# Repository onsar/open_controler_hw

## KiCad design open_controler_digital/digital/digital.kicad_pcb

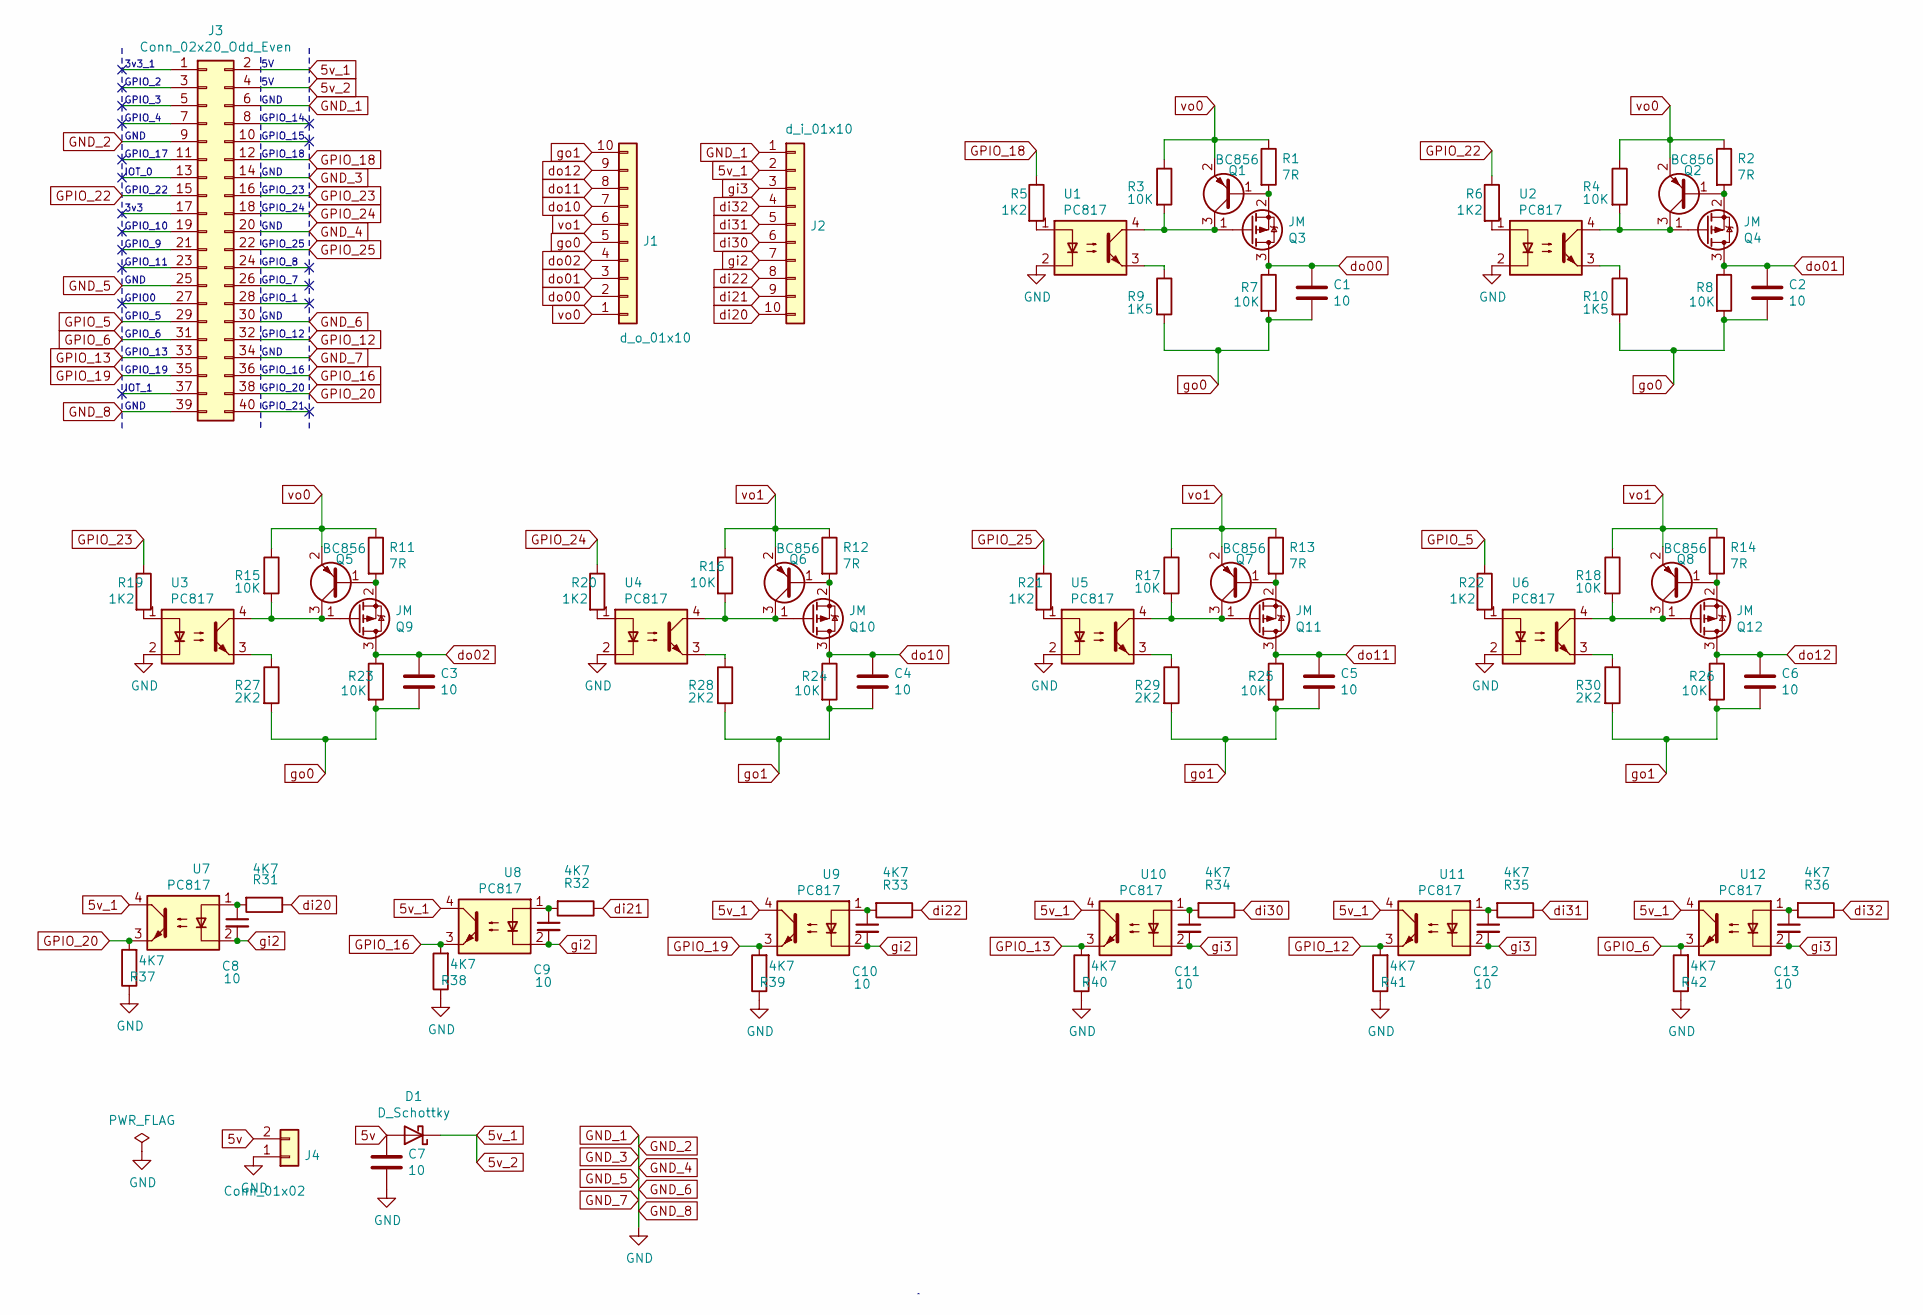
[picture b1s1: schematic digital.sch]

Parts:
C1, C2, C3, C4, C5, C6, C7, C8, C9, C10, C11, C12, C13: 10; C_1206_3216Metric_Pad1.42x1.75mm_HandSolder
D1: D_Schottky; D_2114_3652Metric
J1: d_o_01x10; PhoenixContact_MC_1,5_10-G-3.5_1x10_P3.50mm_Horizontal
J2: d_i_01x10; PhoenixContact_MC_1,5_10-G-3.5_1x10_P3.50mm_Horizontal
J3: Conn_02x20_Odd_Even; PinSocket_2x20_P2.54mm_Vertical
J4: Conn_01x02; PhoenixContact_MC_1,5_2-G-3.5_1x02_P3.50mm_Horizontal
Q1, Q2, Q5, Q6, Q7, Q8: BC856; SOT-23
Q3, Q4, Q9, Q10, Q11, Q12: JM; SOT-23
R1, R2, R11, R12, R13, R14: 7R; R_1206_3216Metric_Pad1.42x1.75mm_HandSolder
R3, R4, R7, R8, R15, R16, R17, R18, R23, R24, R25, R26: 10K; R_1206_3216Metric_Pad1.42x1.75mm_HandSolder
R5, R6, R19, R20, R21, R22: 1K2; R_1206_3216Metric_Pad1.42x1.75mm_HandSolder
R9, R10: 1K5; R_1206_3216Metric_Pad1.42x1.75mm_HandSolder
R27, R28, R29, R30: 2K2; R_1206_3216Metric_Pad1.42x1.75mm_HandSolder
R31, R32, R33, R34, R35, R36, R37, R38, R39, R40, R41, R42: 4K7; R_1206_3216Metric_Pad1.42x1.75mm_HandSolder
U1, U2, U3, U4, U5, U6, U7, U8, U9, U10, U11, U12: PC817; DIP-4_W8.89mm_SMDSocket_LongPads

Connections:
5v: C7.1, D1.2 (A), J4.2
5v_1: D1.1 (K), J2.2, J3.2, J3.4, U7.4, U8.4, U9.4, U10.4, U11.4, U12.4
GND_1: C7.2, J2.1, J3.6, J3.9, J3.14, J3.20, J3.25, J3.30, J3.34, J3.39, J4.1, R37.1, R38.1, R39.1, R40.1, R41.1, R42.1, U1.2, U2.2, U3.2, U4.2, U5.2, U6.2
GPIO_5: J3.29, R22.1
GPIO_6: J3.31, R42.2, U12.3
GPIO_12: J3.32, R41.2, U11.3
GPIO_13: J3.33, R40.2, U10.3
GPIO_16: J3.36, R38.2, U8.3
GPIO_18: J3.12, R5.1
GPIO_19: J3.35, R39.2, U9.3
GPIO_20: J3.38, R37.2, U7.3
GPIO_22: J3.15, R6.1
GPIO_23: J3.16, R19.1
GPIO_24: J3.18, R20.1
GPIO_25: J3.22, R21.1
unnamed: C8.1, R31.2, U7.1
unnamed: C9.1, R32.2, U8.1
unnamed: C10.1, R33.2, U9.1
unnamed: C11.1, R34.2, U10.1
unnamed: C12.1, R35.2, U11.1
unnamed: C13.1, R36.2, U12.1
unnamed: Q1.1 (B), Q3.2 (S), R1.2
unnamed: Q1.3 (C), Q3.1 (G), R3.2, U1.4
unnamed: Q2.1 (B), Q4.2 (S), R2.2
unnamed: Q2.3 (C), Q4.1 (G), R4.2, U2.4
unnamed: Q5.1 (B), Q9.2 (S), R11.2
unnamed: Q5.3 (C), Q9.1 (G), R15.2, U3.4
unnamed: Q6.3 (C), Q10.1 (G), R16.2, U4.4
unnamed: Q6.1 (B), Q10.2 (S), R12.2
unnamed: Q7.3 (C), Q11.1 (G), R17.2, U5.4
unnamed: Q7.1 (B), Q11.2 (S), R13.2
unnamed: Q8.3 (C), Q12.1 (G), R18.2, U6.4
unnamed: Q8.1 (B), Q12.2 (S), R14.2
unnamed: R5.2, U1.1
unnamed: R6.2, U2.1
unnamed: R9.1, U1.3
unnamed: R10.1, U2.3
unnamed: R19.2, U3.1
unnamed: R20.2, U4.1
unnamed: R21.2, U5.1
unnamed: R22.2, U6.1
unnamed: R27.1, U3.3
unnamed: R28.1, U4.3
unnamed: R29.1, U5.3
unnamed: R30.1, U6.3
di20: J2.10, R31.1
di21: J2.9, R32.1
di22: J2.8, R33.1
di30: J2.6, R34.1
di31: J2.5, R35.1
di32: J2.4, R36.1
do00: C1.1, J1.2, Q3.3 (D), R7.1
do01: C2.1, J1.3, Q4.3 (D), R8.1
do02: C3.1, J1.4, Q9.3 (D), R23.1
do10: C4.1, J1.7, Q10.3 (D), R24.1
do11: C5.1, J1.8, Q11.3 (D), R25.1
do12: C6.1, J1.9, Q12.3 (D), R26.1
gi2: C8.2, C9.2, C10.2, J2.7, U7.2, U8.2, U9.2
gi3: C11.2, C12.2, C13.2, J2.3, U10.2, U11.2, U12.2
go0: C1.2, C2.2, C3.2, J1.5, R7.2, R8.2, R9.2, R10.2, R23.2, R27.2
go1: C4.2, C5.2, C6.2, J1.10, R24.2, R25.2, R26.2, R28.2, R29.2, R30.2
vo0: J1.1, Q1.2 (E), Q2.2 (E), Q5.2 (E), R1.1, R2.1, R3.1, R4.1, R11.1, R15.1
vo1: J1.6, Q6.2 (E), Q7.2 (E), Q8.2 (E), R12.1, R13.1, R14.1, R16.1, R17.1, R18.1

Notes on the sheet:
3v3_1
GPIO_2
GPIO_3
GPIO_4
GND
GPIO_17
IOT_0
GPIO_22
3v3
GPIO_10
GPIO_9
GPIO_11
GPIO0
GPIO_5
GPIO_6
GPIO_13
GPIO_19
IOT_1
GPIO_14
GPIO_15
GPIO_18
GPIO_23
GPIO_24
GPIO_25
GPIO_8
GPIO_7
GPIO_1
GPIO_12
GPIO_16
GPIO_20
GPIO_21

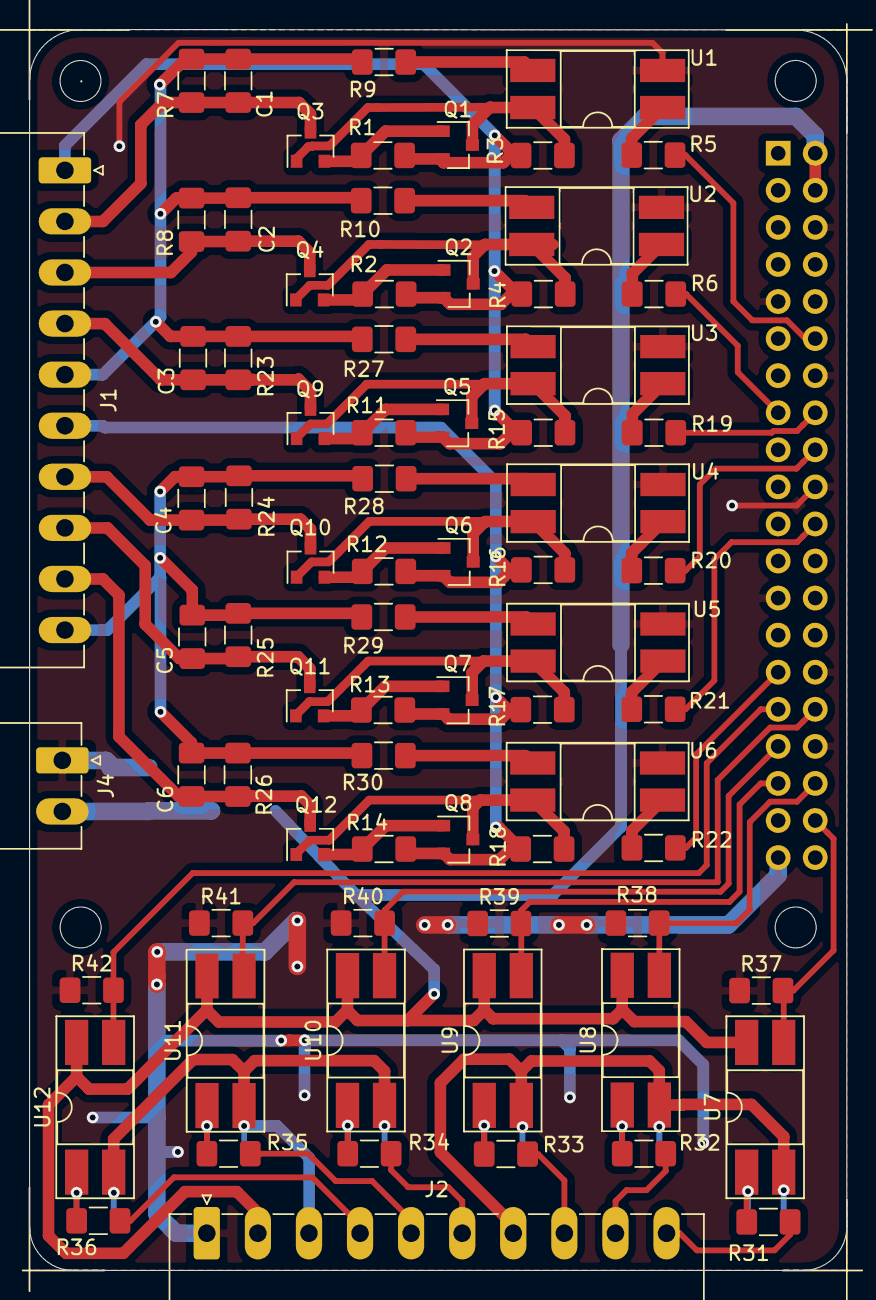
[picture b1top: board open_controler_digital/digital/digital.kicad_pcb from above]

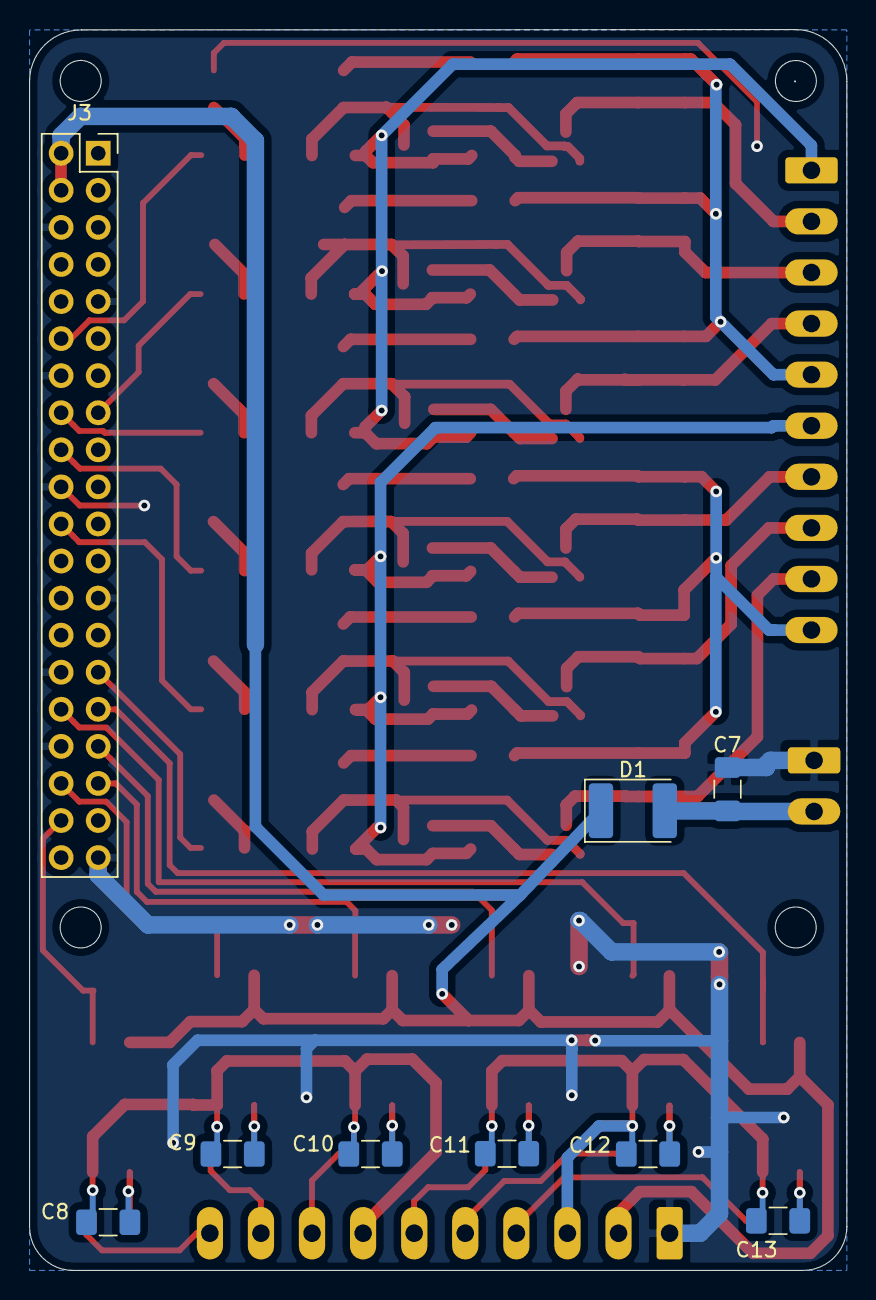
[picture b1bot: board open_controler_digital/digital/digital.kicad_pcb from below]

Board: 2 copper layers, 56.0 x 85.0 mm, 84 parts (9 on the bottom side), 63 nets.

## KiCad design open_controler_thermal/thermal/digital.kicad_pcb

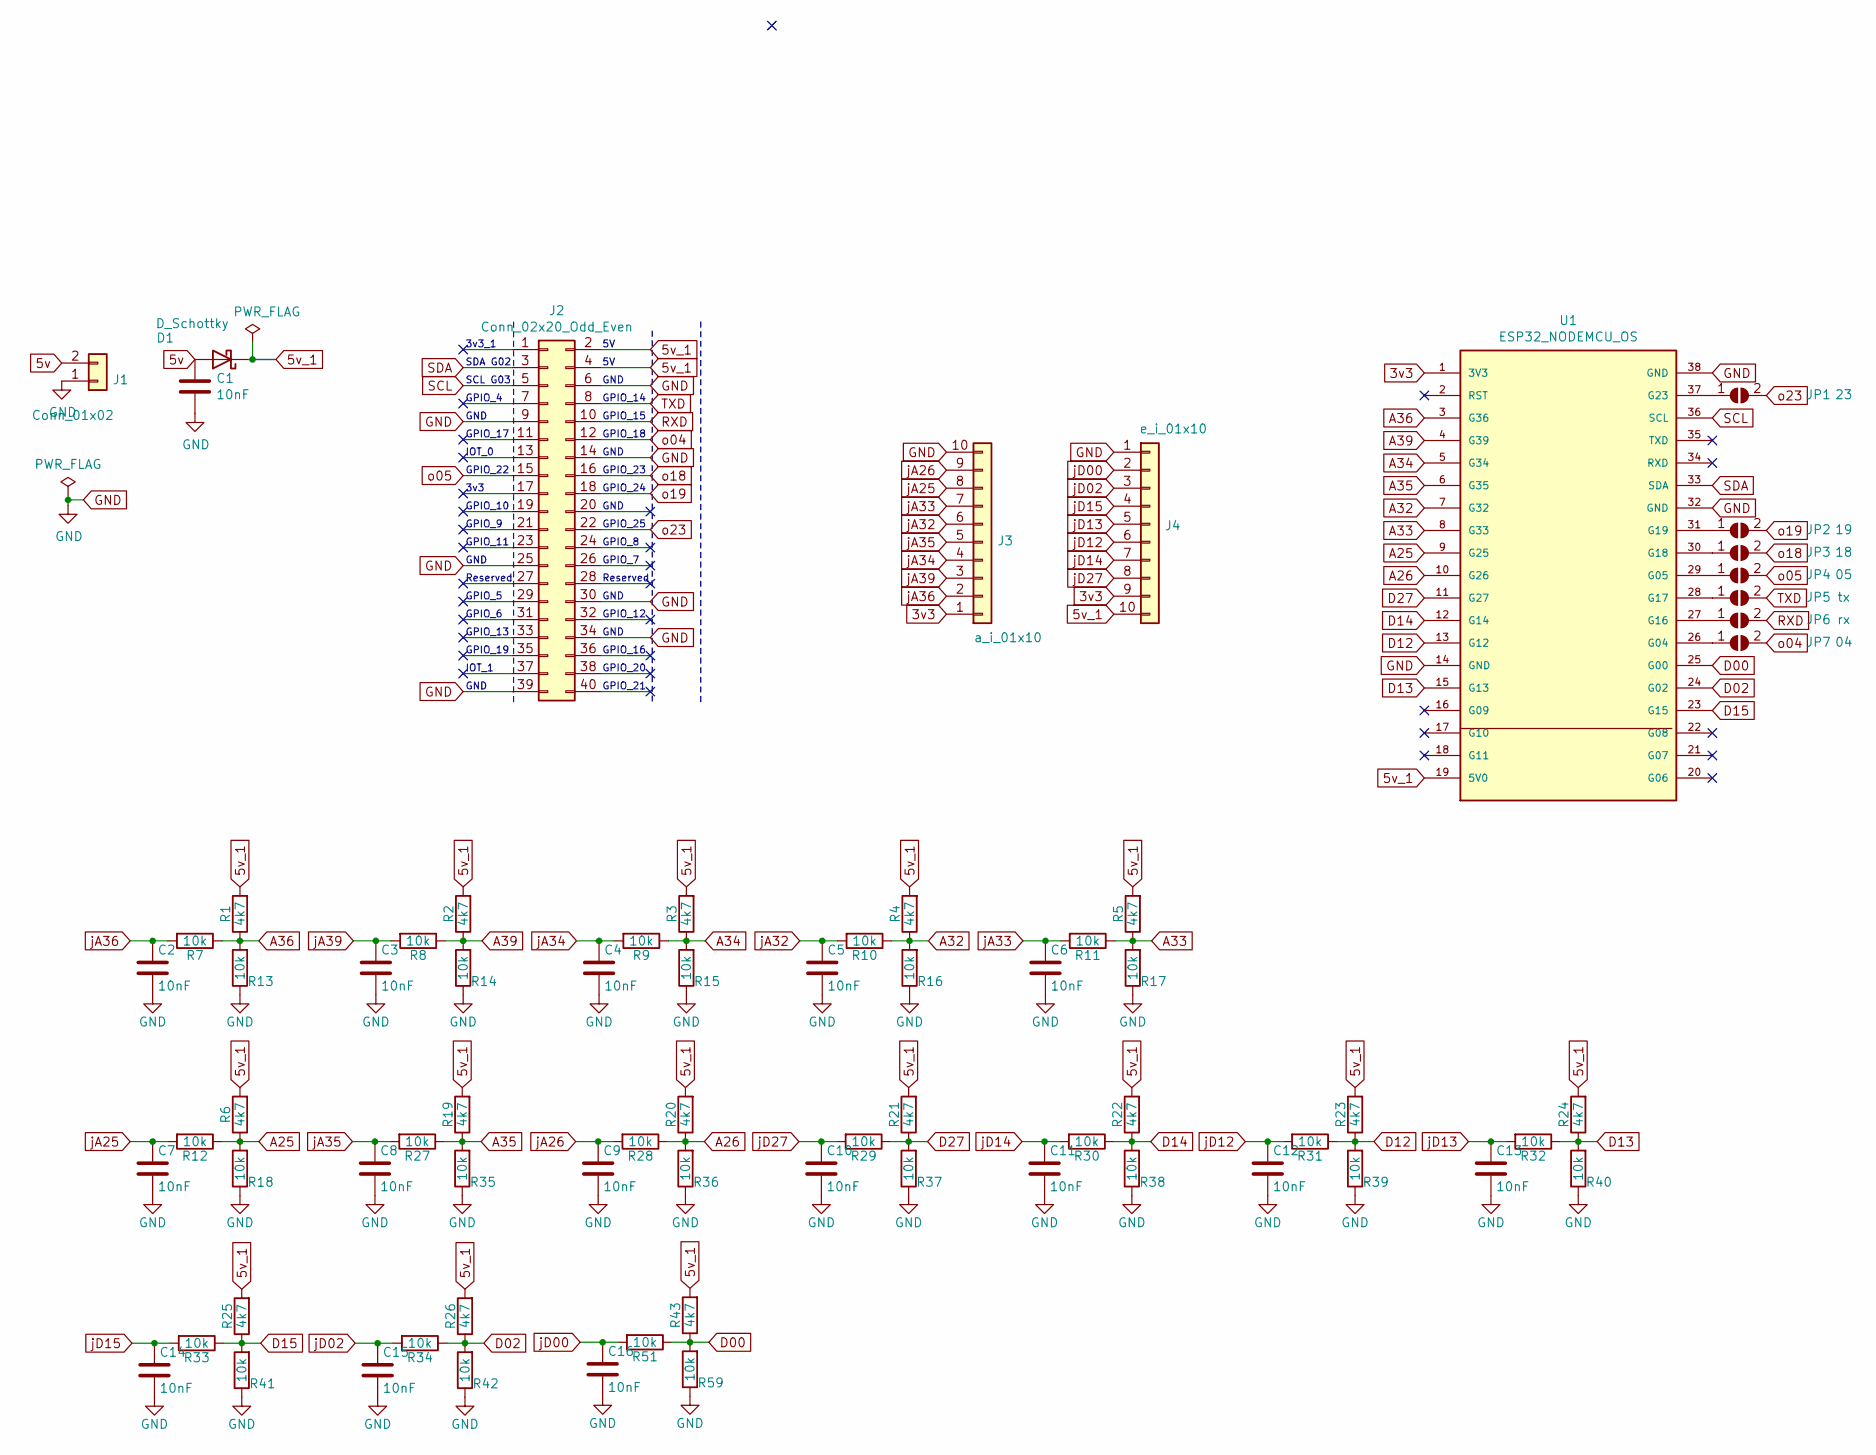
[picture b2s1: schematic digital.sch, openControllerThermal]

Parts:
C1, C2, C3, C4, C5, C6, C7, C8, C9, C10, C11, C12, C13, C14, C15, C16: 10nF; C_1206_3216Metric_Pad1.42x1.75mm_HandSolder
D1: D_Schottky; D_2114_3652Metric
J1: Conn_01x02; PhoenixContact_MC_1,5_2-G-3.5_1x02_P3.50mm_Horizontal
J2: Conn_02x20_Odd_Even; PinSocket_2x20_P2.54mm_Vertical
J3: a_i_01x10; PhoenixContact_MC_1,5_10-G-3.5_1x10_P3.50mm_Horizontal
J4: e_i_01x10; PhoenixContact_MC_1,5_10-G-3.5_1x10_P3.50mm_Horizontal
JP1: 23; SolderJumper-2_P1.3mm_Open_RoundedPad1.0x1.5mm
JP2: 19; SolderJumper-2_P1.3mm_Open_RoundedPad1.0x1.5mm
JP3: 18; SolderJumper-2_P1.3mm_Open_RoundedPad1.0x1.5mm
JP4: 05; SolderJumper-2_P1.3mm_Open_RoundedPad1.0x1.5mm
JP5: tx; SolderJumper-2_P1.3mm_Open_RoundedPad1.0x1.5mm
JP6: rx; SolderJumper-2_P1.3mm_Open_RoundedPad1.0x1.5mm
JP7: 04; SolderJumper-2_P1.3mm_Open_RoundedPad1.0x1.5mm
R1, R2, R3, R4, R5, R6, R19, R20, R21, R22, R23, R24, R25, R26, R43: 4k7; R_1206_3216Metric_Pad1.42x1.75mm_HandSolder
R7, R8, R9, R10, R11, R12, R13, R14, R15, R16, R17, R18, R27, R28, R29, R30, R31, R32, R33, R34, R35, R36, R37, R38, R39, R40, R41, R42, R51, R59: 10k; R_1206_3216Metric_Pad1.42x1.75mm_HandSolder
U1: ESP32_NODEMCU_OS; ESP32-DevKitC

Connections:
3v3: J3.1, J4.9, U1.1 (3V3)
5v: C1.1, D1.2 (A), J1.2
5v_1: D1.1 (K), J2.2, J2.4, J4.10, R1.2, R2.2, R3.2, R4.2, R5.2, R6.2, R19.2, R20.2, R21.2, R22.2, R23.2, R24.2, R25.2, R26.2, R43.2, U1.19 (5V0)
A25: R6.1, R12.1, R18.2, U1.9 (G25)
A26: R20.1, R28.1, R36.2, U1.10 (G26)
A32: R4.1, R10.1, R16.2, U1.7 (G32)
A33: R5.1, R11.1, R17.2, U1.8 (G33)
A34: R3.1, R9.1, R15.2, U1.5 (G34)
A35: R19.1, R27.1, R35.2, U1.6 (G35)
A36: R1.1, R7.1, R13.2, U1.3 (G36)
A39: R2.1, R8.1, R14.2, U1.4 (G39)
D00: R43.1, R51.1, R59.2, U1.25 (G00)
D02: R26.1, R34.1, R42.2, U1.24 (G02)
D12: R23.1, R31.1, R39.2, U1.13 (G12)
D13: R24.1, R32.1, R40.2, U1.15 (G13)
D14: R22.1, R30.1, R38.2, U1.12 (G14)
D15: R25.1, R33.1, R41.2, U1.23 (G15)
D27: R21.1, R29.1, R37.2, U1.11 (G27)
GND: C1.2, C2.2, C3.2, C4.2, C5.2, C6.2, C7.2, C8.2, C9.2, C10.2, C11.2, C12.2, C13.2, C14.2, C15.2, C16.2, J1.1, J2.6, J2.9, J2.14, J2.25, J2.30, J2.34, J2.39, J3.10, J4.1, R13.1, R14.1, R15.1, R16.1, R17.1, R18.1, R35.1, R36.1, R37.1, R38.1, R39.1, R40.1, R41.1, R42.1, R59.1, U1.14 (GND), U1.32 (GND), U1.38 (GND)
unnamed: JP1.1 (A), U1.37 (G23)
unnamed: JP2.1 (A), U1.31 (G19)
unnamed: JP3.1 (A), U1.30 (G18)
unnamed: JP4.1 (A), U1.29 (G05)
unnamed: JP5.1 (A), U1.28 (G17)
unnamed: JP6.1 (A), U1.27 (G16)
unnamed: JP7.1 (A), U1.26 (G04)
RXD: J2.10, JP6.2 (B)
SCL: J2.5, U1.36 (SCL)
SDA: J2.3, U1.33 (SDA)
TXD: J2.8, JP5.2 (B)
jA25: C7.1, J3.8, R12.2
jA26: C9.1, J3.9, R28.2
jA32: C5.1, J3.6, R10.2
jA33: C6.1, J3.7, R11.2
jA34: C4.1, J3.4, R9.2
jA35: C8.1, J3.5, R27.2
jA36: C2.1, J3.2, R7.2
jA39: C3.1, J3.3, R8.2
jD00: C16.1, J4.2, R51.2
jD02: C15.1, J4.3, R34.2
jD12: C12.1, J4.6, R31.2
jD13: C13.1, J4.5, R32.2
jD14: C11.1, J4.7, R30.2
jD15: C14.1, J4.4, R33.2
jD27: C10.1, J4.8, R29.2
o04: J2.12, JP7.2 (B)
o05: J2.15, JP4.2 (B)
o18: J2.16, JP3.2 (B)
o19: J2.18, JP2.2 (B)
o23: J2.22, JP1.2 (B)

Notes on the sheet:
3v3_1
SDA G02
SCL G03
GPIO_4
GND
GPIO_17
IOT_0
GPIO_22
3v3
GPIO_10
GPIO_9
GPIO_11
Reserved
GPIO_5
GPIO_6
GPIO_13
GPIO_19
IOT_1
GPIO_14
GPIO_15
GPIO_18
GPIO_23
GPIO_24
GPIO_25
GPIO_8
GPIO_7
GPIO_12
GPIO_16
GPIO_20
GPIO_21

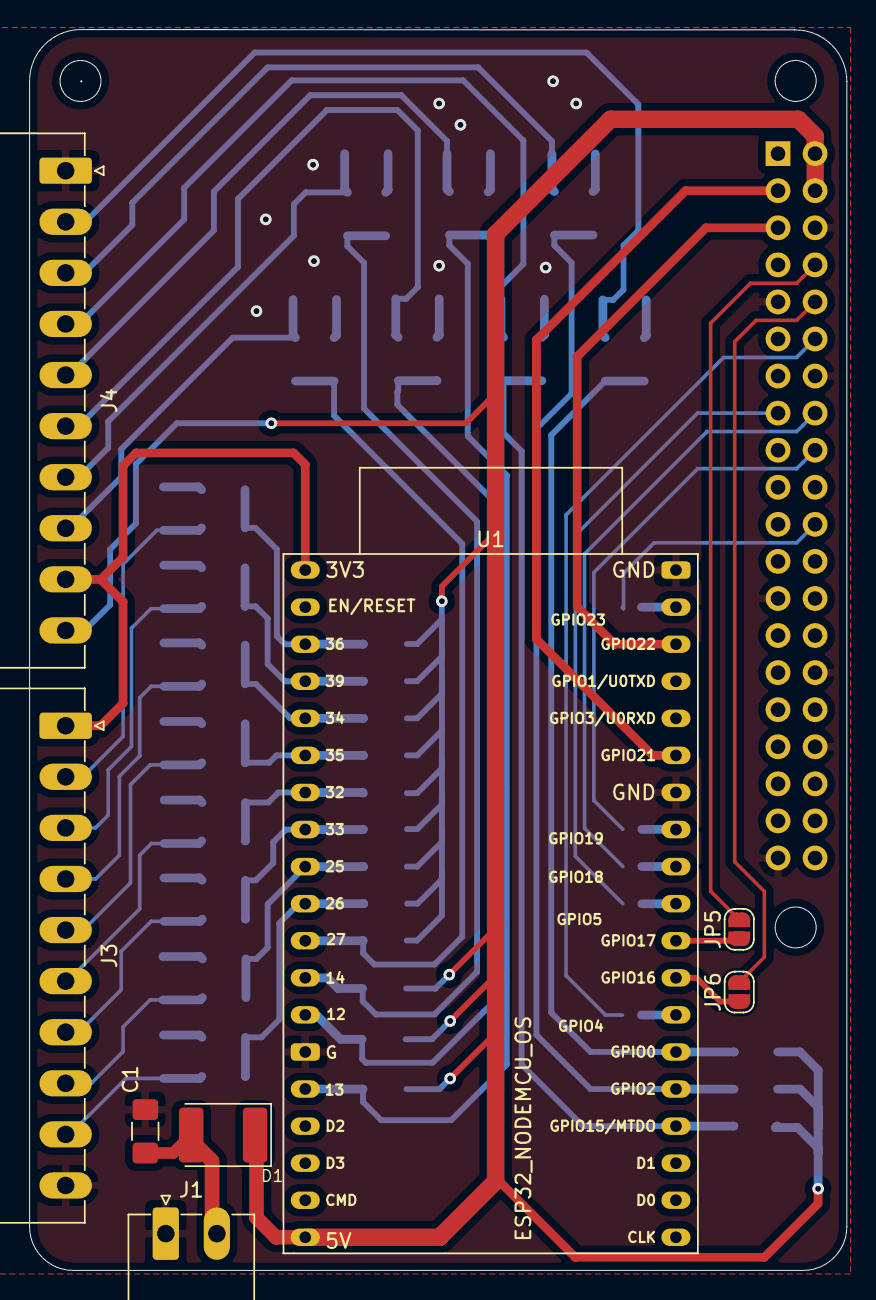
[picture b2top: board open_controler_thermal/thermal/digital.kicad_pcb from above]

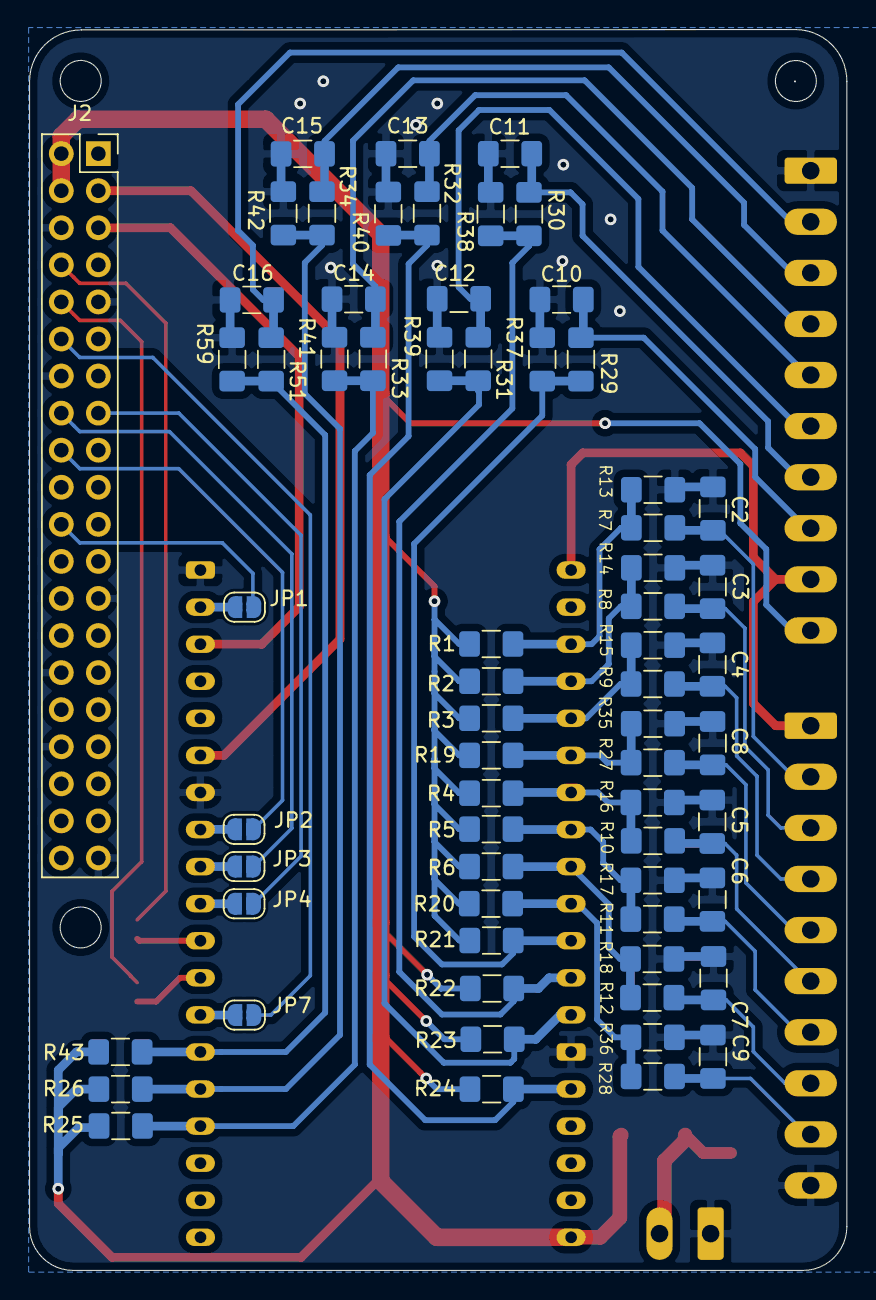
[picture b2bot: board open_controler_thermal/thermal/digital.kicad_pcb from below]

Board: 2 copper layers, 56.0 x 85.0 mm, 74 parts (66 on the bottom side), 50 nets.

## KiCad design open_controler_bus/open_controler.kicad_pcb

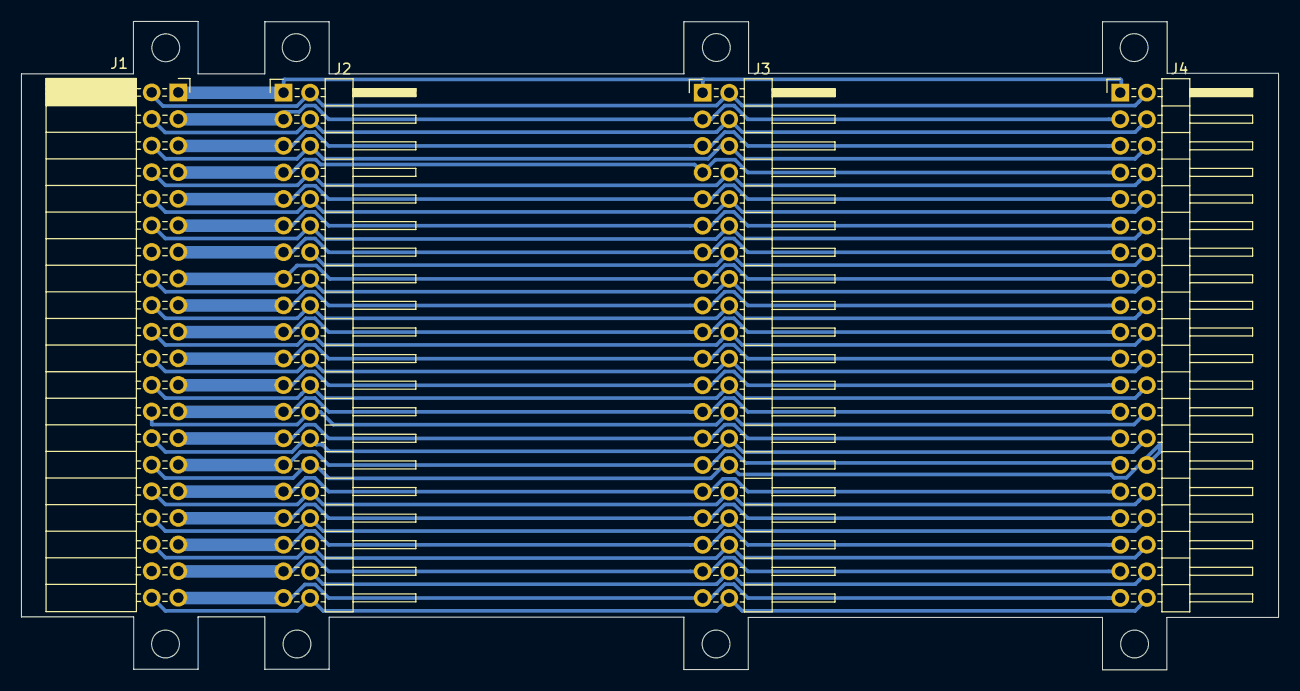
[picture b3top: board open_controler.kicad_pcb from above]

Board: 2 copper layers, 120.1 x 61.9 mm, 4 parts (0 on the bottom side), 40 nets.

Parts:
J1: Conn_02x20_Odd_Even; PinSocket_2x20_P2.54mm_Horizontal
J2, J3, J4: Conn_02x20_Odd_Even; PinHeader_2x20_P2.54mm_Horizontal

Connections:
3v3_1: J1.2, J2.2, J3.2, J4.2
3v3_2: J1.18, J2.18, J3.18, J4.18
5v_1: J1.1, J2.1, J3.1, J4.1
5v_2: J1.3, J2.3, J3.3, J4.3
GND_1: J1.5, J2.5, J3.5, J4.5
GND_2: J1.10, J2.10, J3.10, J4.10
GND_3: J1.13, J2.13, J3.13, J4.13
GND_4: J1.19, J2.19, J3.19, J4.19
GND_5: J1.26, J2.26, J3.26, J4.26
GND_6: J1.29, J2.29, J3.29, J4.29
GND_7: J1.33, J2.33, J3.33, J4.33
GND_8: J1.40, J2.40, J3.40, J4.40
GPIO_0: J1.28, J2.28, J3.28, J4.28
GPIO_1: J1.27, J2.27, J3.27, J4.27
GPIO_2: J1.4, J2.4, J3.4, J4.4
GPIO_3: J1.6, J2.6, J3.6, J4.6
GPIO_4: J1.8, J2.8, J3.8, J4.8
GPIO_5: J1.30, J2.30, J3.30, J4.30
GPIO_6: J1.32, J2.32, J3.32, J4.32
GPIO_7: J1.25, J2.25, J3.25, J4.25
GPIO_8: J1.23, J2.23, J3.23, J4.23
GPIO_9: J1.22, J2.22, J3.22, J4.22
GPIO_10: J1.20, J2.20, J3.20, J4.20
GPIO_11: J1.24, J2.24, J3.24, J4.24
GPIO_12: J1.31, J2.31, J3.31, J4.31
GPIO_13: J1.34, J2.34, J3.34, J4.34
GPIO_14: J1.7, J2.7, J3.7, J4.7
GPIO_15: J1.9, J2.9, J3.9, J4.9
GPIO_16: J1.35, J2.35, J3.35, J4.35
GPIO_17: J1.12, J2.12, J3.12, J4.12
GPIO_18: J1.11, J2.11, J3.11, J4.11
GPIO_19: J1.36, J2.36, J3.36, J4.36
GPIO_20: J1.37, J2.37, J3.37, J4.37
GPIO_21: J1.39, J2.39, J3.39, J4.39
GPIO_22: J1.16, J2.16, J3.16, J4.16
GPIO_23: J1.15, J2.15, J3.15, J4.15
GPIO_24: J1.17, J2.17, J3.17, J4.17
GPIO_25: J1.21, J2.21, J3.21, J4.21
IO_26: J2.38, J3.38, J4.38
IO_27: J2.14, J3.14, J4.14

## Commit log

2022-01-15 primer commit
2022-06-16 avances en la pcb
2022-06-19 desarrollando hw, limitador de intensidad
2022-07-01 avanzando con el limitador de intensidad
2022-07-15 avances pcb digital
2022-07-27 desarrollo de la PCB con la huella de la Raspberry
2022-07-28 version de hw operativa
2022-07-28 version para fabricacion
2022-07-29 version enviada a fabricar
2022-09-12 trabajando en thermal
2022-09-14 trabajando en la huella del ESP32
2022-09-15 diseñando PCB thermal con ESP32
2023-01-16 trabajando en openControllerDigital
2023-05-24 version fabricada de open_controles_thermal
2025-07-07 3d anadido a open controles bus
2025-07-10 ecotherm. actualizacion de los conectores phenix
2025-07-10 ecotherm. actualizacion del conector del bus
2025-07-10 digital. actualización de los conectores 3d
